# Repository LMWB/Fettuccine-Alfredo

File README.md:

# Fettuccine-Alfredo
very basic and cheap constant current circuit for medium power LED's

This project is about to design a very simple LED driver circuit for medium power LED's. I'd like to play around with different LED color temperatures and shapes. 

# Simulations and Schematics

# Adjusting Current
```math
I_{LED} \approx I_{R_S} = \frac{U_{D} - U_{BE}}{R_S}  
```

```math
I_{LED} = \frac{1.8 V - 0.7 V}{100 \Omega} = 11mA  
```

## Revision 0 uses PLCC 2835 LED Footprint and 3528 (alternative)

## Revision 1 uses 3528 Footprint only

# Real World Examples
## Street Light
## Lamp
I used the [timer clock project](https://github.com/LMWB/Cannelloni-al-Forno) and three of this LED boards to create a illumination of my courtyard.  

## X-Mas Star
I also used the [timer clock project](https://github.com/LMWB/Cannelloni-al-Forno) and three of this LED boards in a three-dimensional setup to create a kind of LED light build to use in a outdoor christmas decoration.  

# Sources
## Material
high performance power LED found on ebay

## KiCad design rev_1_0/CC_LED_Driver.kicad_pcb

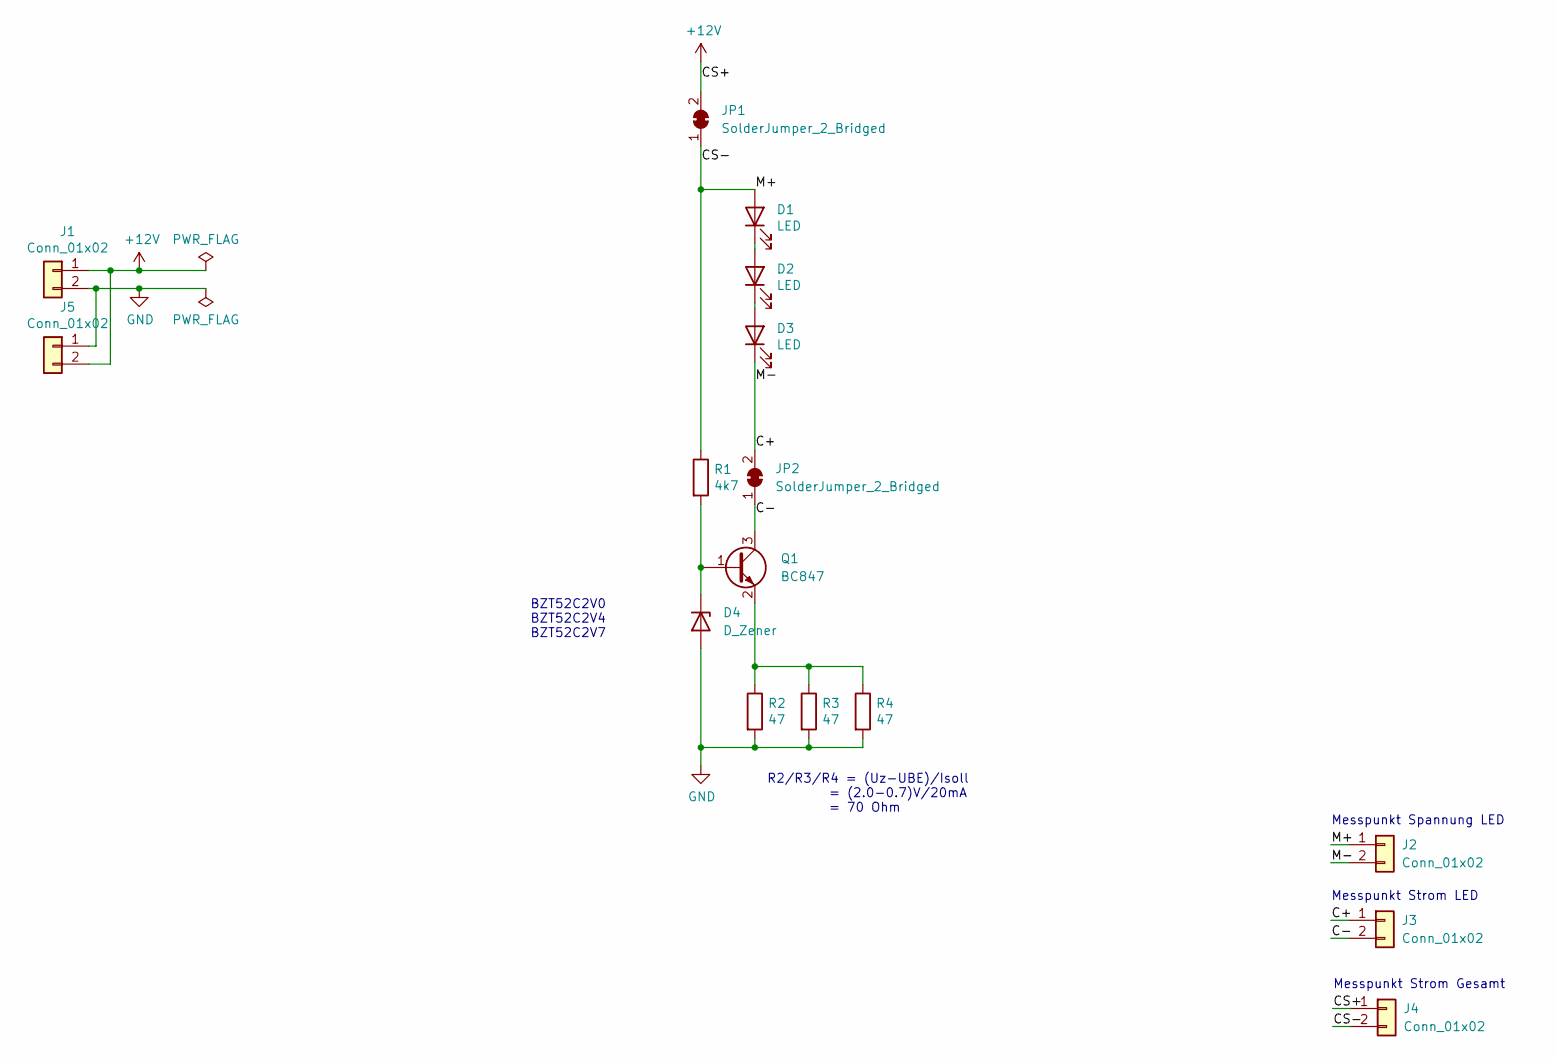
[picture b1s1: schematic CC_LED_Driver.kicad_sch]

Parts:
D1, D2, D3: LED; LED_3528_Handsolder_XL
D4: D_Zener; D_SOD-123_HandsolderXL
J1, J5: Conn_01x02; PinHeader_1x02_P2.54mm_Horizontal
J2, J3, J4: Conn_01x02; PinHeader_1x02_P2.54mm_Vertical
JP1, JP2: SolderJumper_2_Bridged; SolderJumper-2_P1.3mm_Bridged2Bar_RoundedPad1.0x1.5mm
Q1: BC847; SOT-23_Handsoldering
R1: 4k7; R_1206_3216Metric_Pad1.30x1.75mm_HandSolder
R2, R3, R4: 47; R_1206_3216Metric_Pad1.30x1.75mm_HandSolder

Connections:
+12V: J1.1, J4.1, J5.2, JP1.2 (B)
/C+: D3.1 (K), J2.2, J3.1, JP2.2 (B)
/C-: J3.2, JP2.1 (A), Q1.3 (C)
/CS-: D1.2 (A), J2.1, J4.2, JP1.1 (A), R1.1
GND: D4.2 (A), J1.2, J5.1, R2.2, R3.2, R4.2
unnamed: D1.1 (K), D2.2 (A)
unnamed: D2.1 (K), D3.2 (A)
unnamed: D4.1 (K), Q1.1 (B), R1.2
unnamed: Q1.2 (E), R2.1, R3.1, R4.1

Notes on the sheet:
R2/R3/R4 = (Uz-UBE)/Isoll = (2.0-0.7)V/20mA = 70 Ohm
Messpunkt Strom LED
BZT52C2V0 BZT52C2V4 BZT52C2V7
Messpunkt Spannung LED
Messpunkt Strom Gesamt

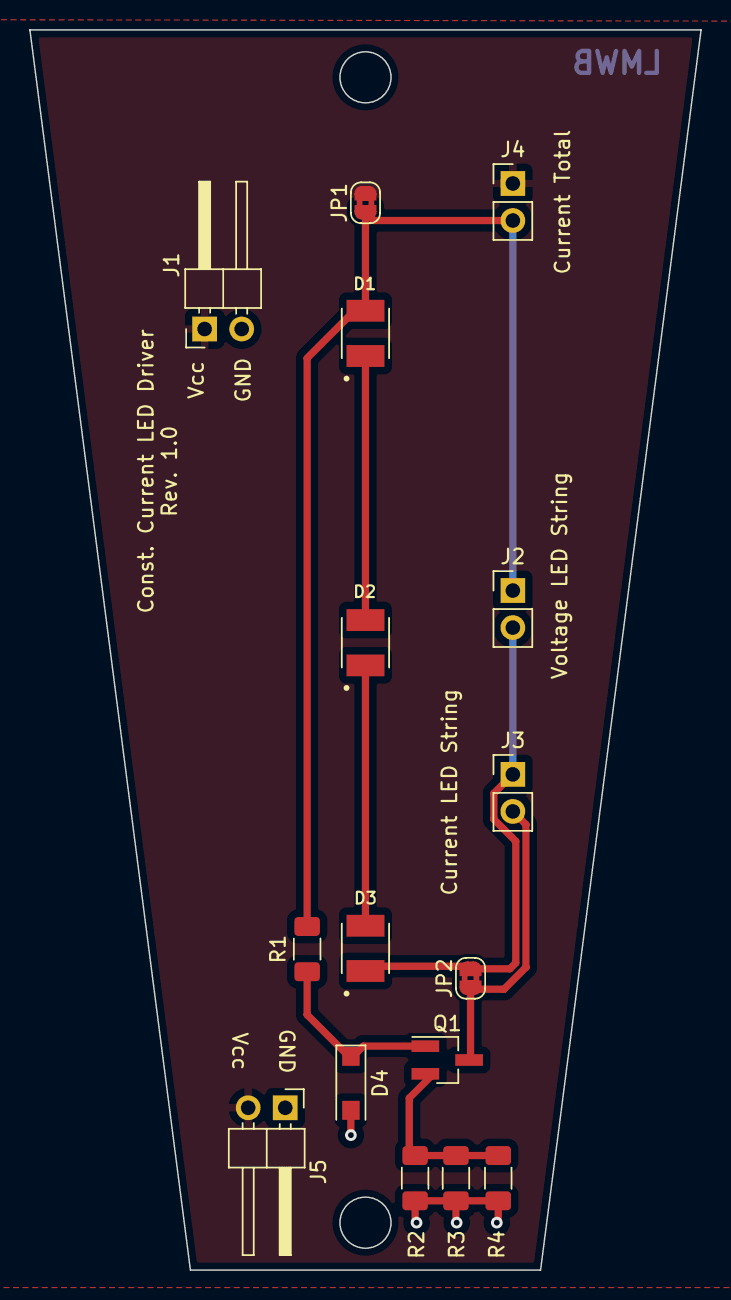
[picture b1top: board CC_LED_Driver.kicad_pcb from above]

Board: 2 copper layers, 46.0 x 85.0 mm, 16 parts (0 on the bottom side), 9 nets.

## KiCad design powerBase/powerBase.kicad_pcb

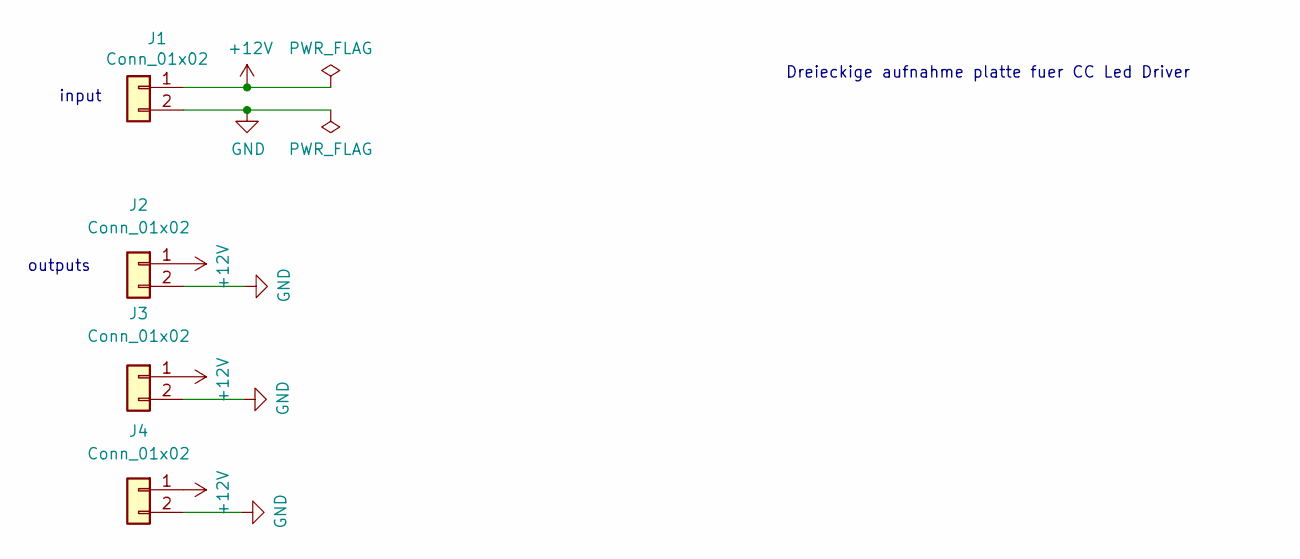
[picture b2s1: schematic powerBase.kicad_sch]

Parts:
J1, J2, J3, J4: Conn_01x02; PinHeader_1x02_P2.54mm_Vertical

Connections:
+12V: J1.1, J2.1, J3.1, J4.1
GND: J1.2, J2.2, J3.2, J4.2

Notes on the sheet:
Dreieckige aufnahme platte fuer CC Led Driver
input
outputs

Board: 2 copper layers, 4 parts (0 on the bottom side), 2 nets, no tracks yet.

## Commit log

2024-07-01 add kicad files
2024-07-01 added LTSpice Simulation
2024-11-25 added images, update readme
2024-12-23 added spice results and math
2024-12-23 added schematics
2024-12-23 README.md aktualisieren
2025-01-14 check documentation
2025-02-06 added images of x-mas star
2025-02-06 remove text
